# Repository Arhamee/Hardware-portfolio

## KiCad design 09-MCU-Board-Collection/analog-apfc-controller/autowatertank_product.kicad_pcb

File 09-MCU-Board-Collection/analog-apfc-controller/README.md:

# Analog Process Automation Controller

Fully analog automation system — no microcontroller, no firmware — built
entirely from discrete logic.

## Function
Automates a liquid-filling process: turns on a pump at regular intervals,
checks for flow, detects tank-full state, and safely controls AC appliances.

## How It Works
| IC | Role |
|---|---|
| NE555 #1 | 30-minute interval timer (astable) |
| NE555 #2 | Intermediate latch/controller based on flow detection |
| NE555 #3 | Final appliance state control based on sensor feedback |
| BC547 stage | Tank-full detection via probe contact sensing |
| 5× relays | Sequencing and isolation for safe AC control |

## Why This Project
A deliberate exercise in analog system design — showing what's achievable
with discrete components and timing logic alone, no code or bootloader
involved.

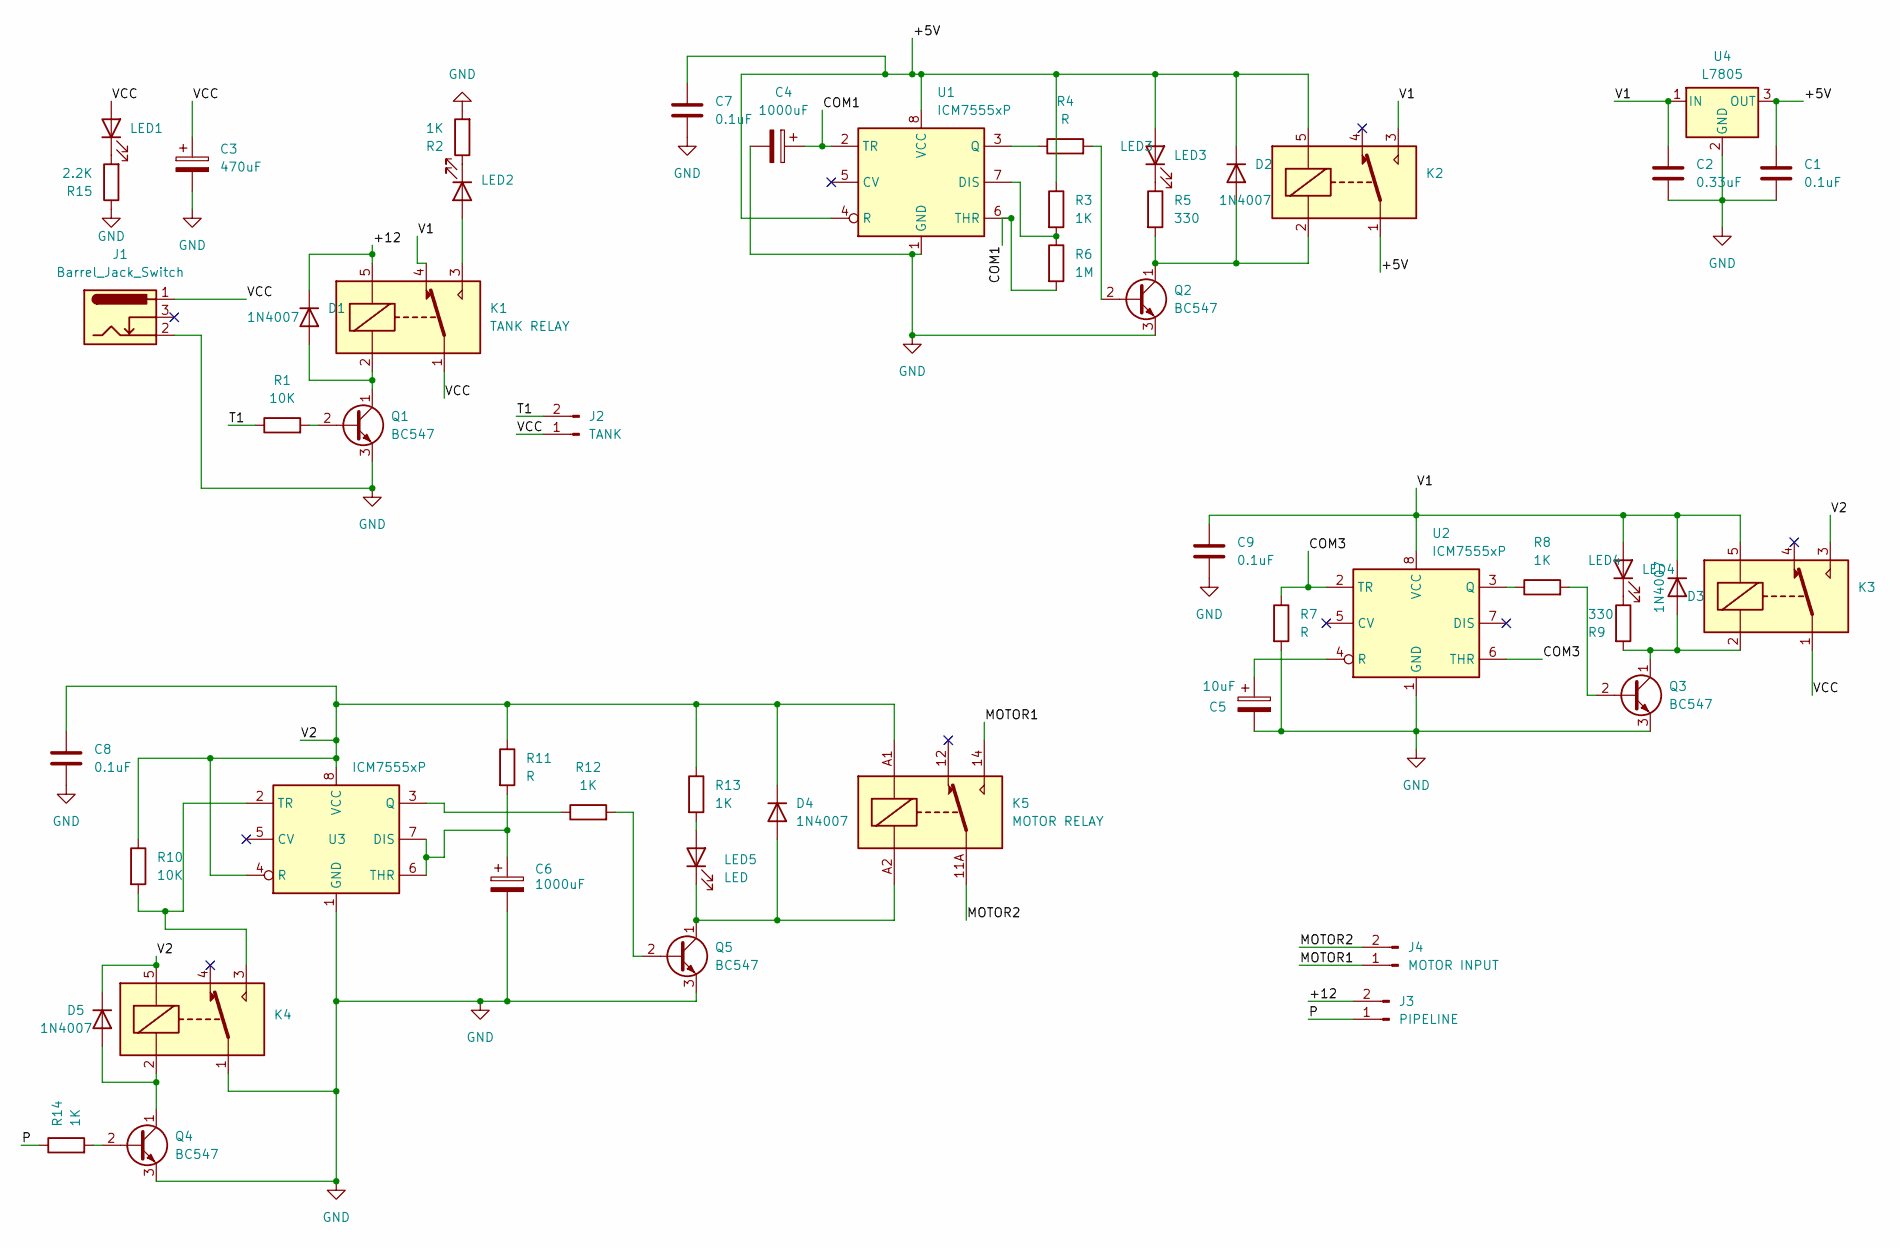
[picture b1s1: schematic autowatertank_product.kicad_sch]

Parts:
C1, C7, C8, C9: 0.1uF; C_Disc_D3.0mm_W2.0mm_P2.50mm
C2: 0.33uF; C_Disc_D3.0mm_W2.0mm_P2.50mm
C3: 470uF; CP_Radial_D8.0mm_P3.50mm
C4, C6: 1000uF; CP_Radial_D8.0mm_P5.00mm
C5: 10uF; CP_Radial_D4.0mm_P2.00mm
D1, D2, D3, D4, D5: 1N4007; D_DO-41_SOD81_P10.16mm_Horizontal
J1: Barrel_Jack_Switch; BarrelJack_GCT_DCJ200-10-A_Horizontal
J2: TANK; TerminalBlock_MaiXu_MX126-5.0-02P_1x02_P5.00mm
J3: PIPELINE; TerminalBlock_MaiXu_MX126-5.0-02P_1x02_P5.00mm
J4: MOTOR INPUT; TerminalBlock_MaiXu_MX126-5.0-02P_1x02_P5.00mm
K1: TANK RELAY; Relay_SPDT_SANYOU_SRD_Series_Form_C
K2: 555 IC RELAY 1; Relay_SPDT_SANYOU_SRD_Series_Form_C
K3, K4: Relay_SPDT_SANYOU_SRD_Series_Form_C
K5: MOTOR RELAY; Relay_SPDT_RAYEX-L90
LED1: LED_D5.0mm_Clear
LED2: FULL; LED_D5.0mm_Clear
LED3: LED3; LED_D5.0mm_Clear
LED4: LED4; LED_D5.0mm_Clear
LED5: LED; LED_D5.0mm_Clear
Q1, Q2, Q3, Q4, Q5: BC547; TO-92_Inline
R1, R10: 10K; R_Axial_DIN0207_L6.3mm_D2.5mm_P10.16mm_Horizontal
R2, R3, R8, R12, R13, R14: 1K; R_Axial_DIN0207_L6.3mm_D2.5mm_P10.16mm_Horizontal
R4, R7, R11: R; R_Axial_DIN0207_L6.3mm_D2.5mm_P10.16mm_Horizontal
R5, R9: 330; R_Axial_DIN0207_L6.3mm_D2.5mm_P10.16mm_Horizontal
R6: 1M; R_Axial_DIN0207_L6.3mm_D2.5mm_P10.16mm_Horizontal
R15: 2.2K; R_Axial_DIN0207_L6.3mm_D2.5mm_P10.16mm_Horizontal
U1, U2, U3: ICM7555xP; DIP-8_W7.62mm
U4: L7805; TO-220-3_Vertical

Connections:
/+5V: C1.1, C7.1, D2.1 (K), K2.1, K2.5, LED3.2 (A), R3.1, U1.4 (R), U1.8 (VCC), U4.3 (OUT)
/+12: D1.1 (K), J3.2, K1.5
/COM1: C4.1, R6.2, U1.2 (TR), U1.6 (THR)
/COM3: R7.1, U2.2 (TR), U2.6 (THR)
/MOTOR1: J4.1, K5.14
/MOTOR2: J4.2, K5.11A, K5.11B
/P: J3.1, R14.1
/T1: J2.2, R1.1
/V1: C2.1, C9.1, D3.1 (K), K1.4, K2.3, K3.5, LED4.2 (A), U2.8 (VCC), U4.1 (IN)
/V2: C8.1, D4.1 (K), D5.1 (K), K3.3, K4.5, K5.A1, R10.1, R11.1, R13.1, U3.4 (R), U3.8 (VCC)
/VCC: C3.1, J1.1, J2.1, K1.1, K3.1, LED1.2 (A)
GND: C1.2, C2.2, C3.2, C4.2, C5.2, C6.2, C7.2, C8.2, C9.2, J1.2, K4.1, Q1.3 (E), Q2.3 (E), Q3.3 (E), Q4.3 (E), Q5.3 (E), R2.2, R7.2, R15.1, U1.1 (GND), U2.1 (GND), U3.1 (GND), U4.2 (GND)
unnamed: D1.2 (A), K1.2, Q1.1 (C)
unnamed: D2.2 (A), K2.2, Q2.1 (C), R5.2
unnamed: D3.2 (A), K3.2, Q3.1 (C), R9.2
unnamed: D4.2 (A), K5.A2, LED5.1 (K), Q5.1 (C)
unnamed: D5.2 (A), K4.2, Q4.1 (C)
unnamed: LED1.1 (K), R15.2
unnamed: K1.3, LED2.2 (A)
unnamed: LED2.1 (K), R2.1
unnamed: LED3.1 (K), R5.1
unnamed: LED4.1 (K), R9.1
unnamed: LED5.2 (A), R13.2
unnamed: Q1.2 (B), R1.2
unnamed: Q2.2 (B), R4.2
unnamed: Q3.2 (B), R8.2
unnamed: Q4.2 (B), R14.2
unnamed: Q5.2 (B), R12.2
unnamed: R3.2, R6.1, U1.7 (DIS)
unnamed: R4.1, U1.3 (Q)
unnamed: R8.1, U2.3 (Q)
unnamed: C5.1, U2.4 (R)
unnamed: C6.1, R11.2, U3.6 (THR), U3.7 (DIS)
unnamed: R12.1, U3.3 (Q)
unnamed: K4.3, R10.2, U3.2 (TR)

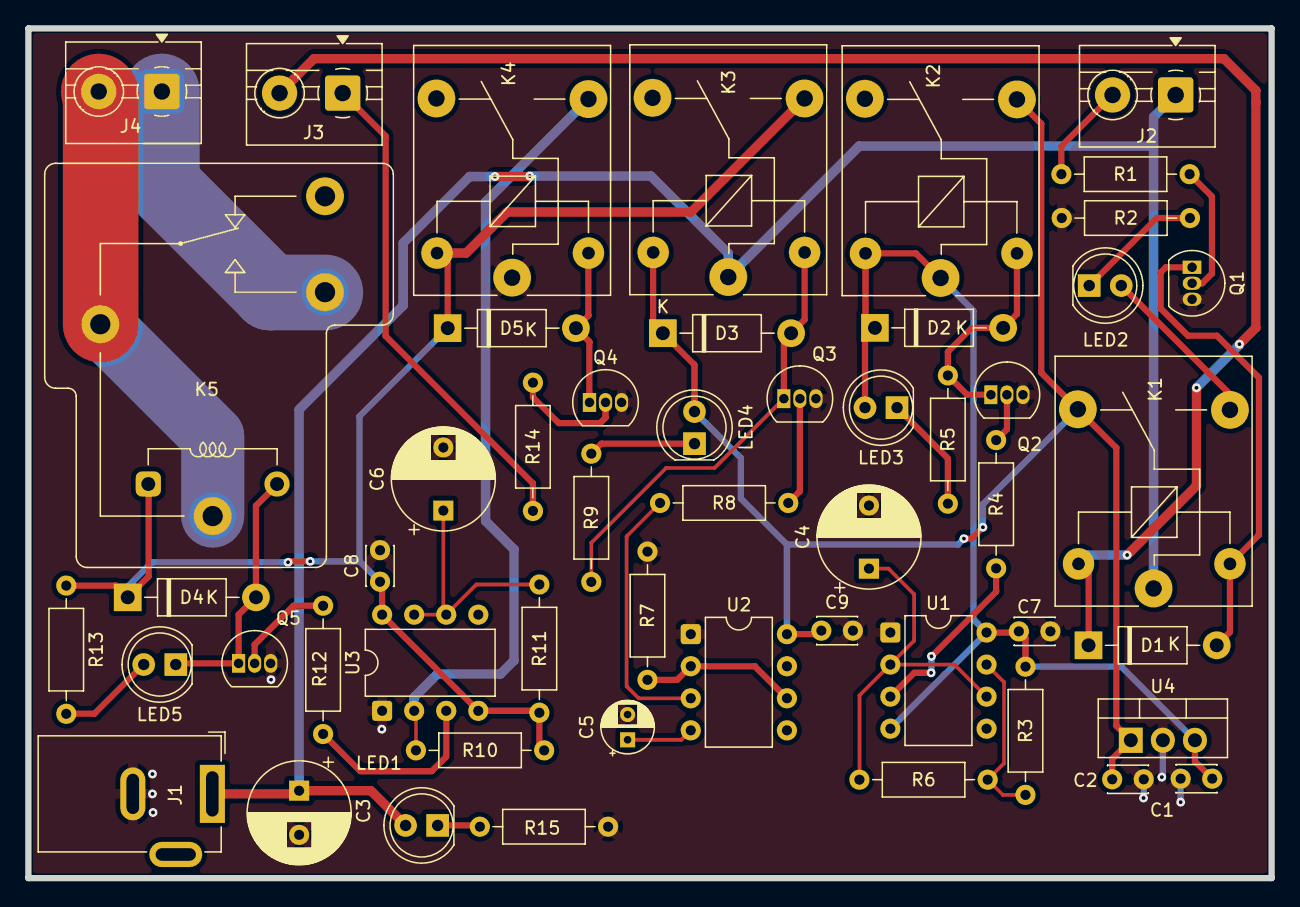
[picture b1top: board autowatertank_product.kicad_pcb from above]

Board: 2 copper layers, 98.5 x 67.3 mm, 52 parts (0 on the bottom side), 35 nets.

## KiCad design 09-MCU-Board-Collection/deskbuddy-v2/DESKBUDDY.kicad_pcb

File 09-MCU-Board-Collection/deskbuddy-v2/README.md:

# DeskBuddy v2

Custom PCB replacing a breadboard prototype's separate modules with a
single integrated board.

## What Got Replaced
- Separate charging module → **IP5306** (charges, protects, and boosts to 5V — one chip)
- Standalone touch sensor breakout → **TTP223** etched directly onto the board
- Breakout boards and jumper wires → clean, compact PCB

## Features
- ESP32-C3 + OLED display
- Live battery indicator on-screen
- Animated eyes with expressions
- Real-time weather with custom icons
- Auto-syncing clock (timezone-aware)
- Birthday celebration mode

## Note
Started as "let me make my desk less boring" — turned into a full PCB
design exercise in component integration and board miniaturization.

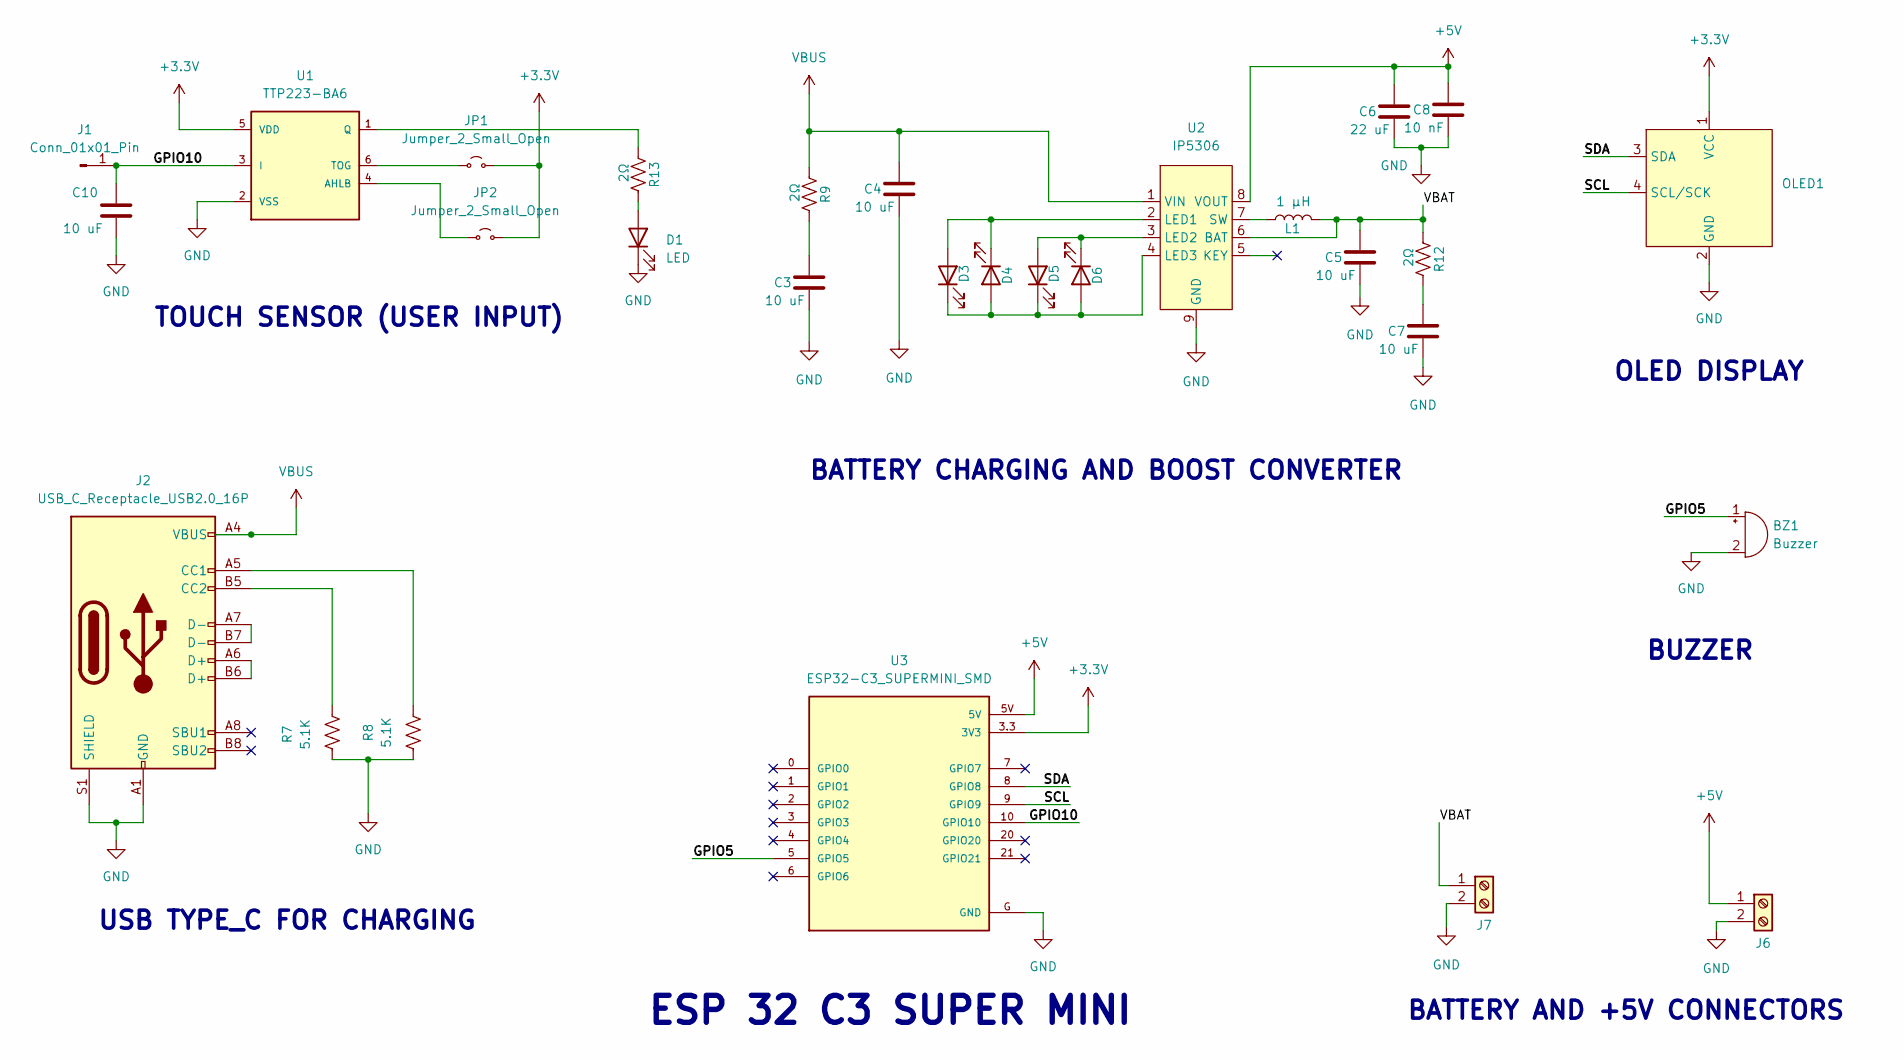
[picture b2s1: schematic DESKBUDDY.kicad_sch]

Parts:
BZ1: Buzzer; Buzzer_12x9.5RM7.6
C3, C4, C5, C7: 10 uF; C_1206_3216Metric_Pad1.33x1.80mm_HandSolder
C6: 22 uF; C_1206_3216Metric_Pad1.33x1.80mm_HandSolder
C8: 10 nF; C_1206_3216Metric_Pad1.33x1.80mm_HandSolder
C10: 10 uF; C_0805_2012Metric_Pad1.18x1.45mm_HandSolder
D1: LED; D_0805_2012Metric_Pad1.15x1.40mm_HandSolder
D3, D4, D5, D6: Blue LED; LED_1206_3216Metric
J1: Conn_01x01_Pin; TestPoint_Pad_D4.0mm
J2: USB_C_Receptacle_USB2.0_16P; USB_C_Receptacle_GCT_USB4105-xx-A_16P_TopMnt_Horizontal
J6, J7: Terminal_01x02; PinHeader_1x02_P2.00mm_Vertical
JP1, JP2: Jumper_2_Small_Open; SolderJumper-2_P1.3mm_Open_Pad1.0x1.5mm
L1: 1 µH; L_Sunlord_SWPA6028S
OLED1: PinSocket_1x04_P2.00mm_Vertical
R7, R8: 5.1K; R_1206_3216Metric
R9, R12: 2Ω; R_1206_3216Metric
R13: 2Ω; R_0805_2012Metric_Pad1.20x1.40mm_HandSolder
U1: TTP223-BA6; SOT23-6
U2: IP5306; SOP-8-1EP_4.57x4.57mm_P1.27mm_EP4.57x4.45mm_ThermalVias
U3: ESP32-C3_SUPERMINI_SMD; MODULE_ESP32-C3_SUPERMINI

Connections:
+3.3V: JP1.2 (B), JP2.2 (B), OLED1.1 (VCC), U1.5 (VDD), U3.3.3 (3V3)
+5V: C6.1, C8.1, J6.1, U2.8 (VOUT), U3.5V
/GPIO5: BZ1.1 (+), U3.5 (GPIO5)
/GPIO10: C10.1, J1.1, U1.3 (I), U3.10 (GPIO10)
/SCL: OLED1.4 (SCL/SCK), U3.9 (GPIO9)
/SDA: OLED1.3 (SDA), U3.8 (GPIO8)
/VBAT: C5.1, J7.1, L1.2, R12.1, U2.6 (BAT)
GND: BZ1.2 (-), C3.2, C4.2, C5.2, C6.2, C7.2, C8.2, C10.2, D1.1 (K), J2.A1 (GND), J2.A12 (GND), J2.B1 (GND), J2.B12 (GND), J2.S1 (SHIELD), J6.2, J7.2, OLED1.2 (GND), R7.1, R8.1, U1.2 (VSS), U2.9 (GND), U3.G (GND)
unnamed: C3.1, R9.2
unnamed: C7.1, R12.2
unnamed: D1.2 (A), R13.2
unnamed: D3.2 (A), D4.1 (K), U2.2 (LED1)
unnamed: D3.1 (K), D4.2 (A), D5.1 (K), D6.2 (A), U2.4 (LED3)
unnamed: D5.2 (A), D6.1 (K), U2.3 (LED2)
unnamed: J2.A5 (CC1), R8.2
unnamed: J2.B5 (CC2), R7.2
unnamed: J2.A6 (D+), J2.B6 (D+)
unnamed: J2.A7 (D-), J2.B7 (D-)
unnamed: JP1.1 (A), U1.6 (TOG)
unnamed: JP2.1 (A), U1.4 (AHLB)
unnamed: R13.1, U1.1 (Q)
unnamed: L1.1, U2.7 (SW)
VBUS: C4.1, J2.A4 (VBUS), J2.A9 (VBUS), J2.B4 (VBUS), J2.B9 (VBUS), R9.1, U2.1 (VIN)

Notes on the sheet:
TOUCH SENSOR (USER INPUT)
BATTERY CHARGING AND BOOST CONVERTER
OLED DISPLAY
BATTERY AND +5V CONNECTORS
USB TYPE_C FOR CHARGING
ESP 32 C3 SUPER MINI
BUZZER

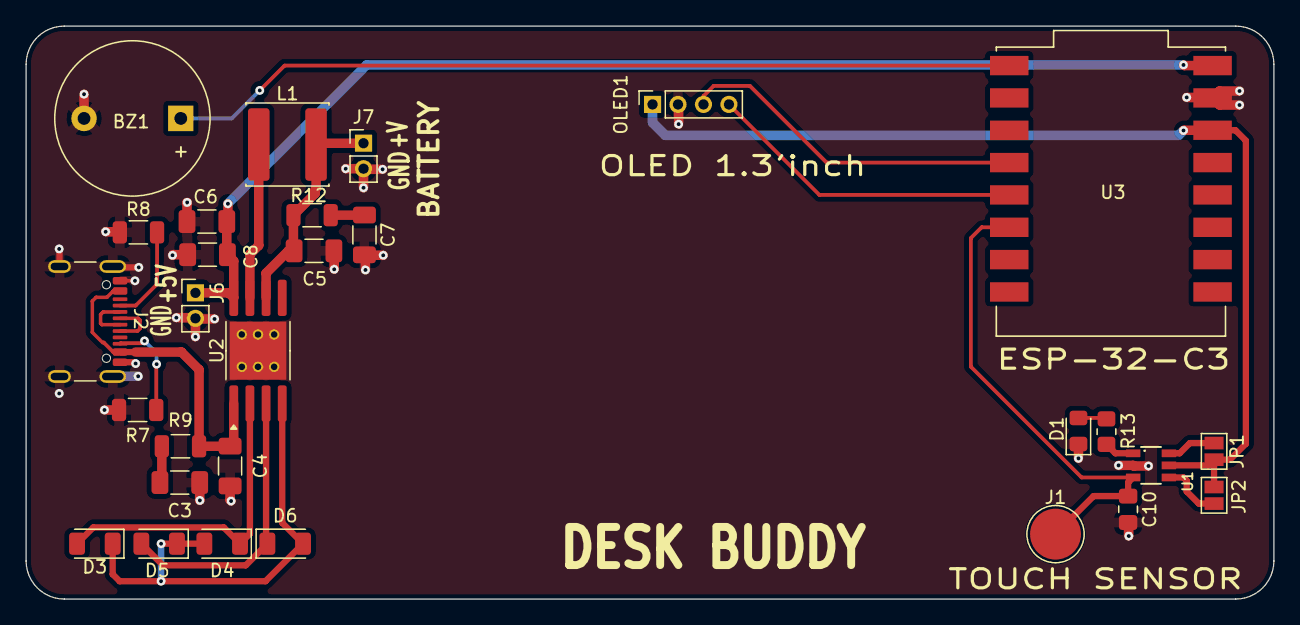
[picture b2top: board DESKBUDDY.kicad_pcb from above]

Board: 2 copper layers, 98.0 x 45.0 mm, 29 parts (0 on the bottom side), 23 nets.

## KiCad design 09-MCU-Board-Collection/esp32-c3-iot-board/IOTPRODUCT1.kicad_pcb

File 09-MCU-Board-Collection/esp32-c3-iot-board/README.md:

# IoT Control Board — ESP32-C3

Custom board combining power electronics and embedded IoT into one design,
plus a companion programming board.

## Power Path
12V input → boost converter → 5V → 3.3V regulation for the ESP32-C3

## Features
- Handles up to 5A load
- Onboard fuse protection
- Integrated T90 relay for high-power switching
- Dashboard integration (QWIN AI) for real-time monitoring and control

## Bonus
A separate USB-to-UART programming board, built alongside this one, for
seamless firmware uploading and debugging.

## What This Covered
End-to-end IoT product design — power management, protection, communication,
and control — not just the MCU layout.

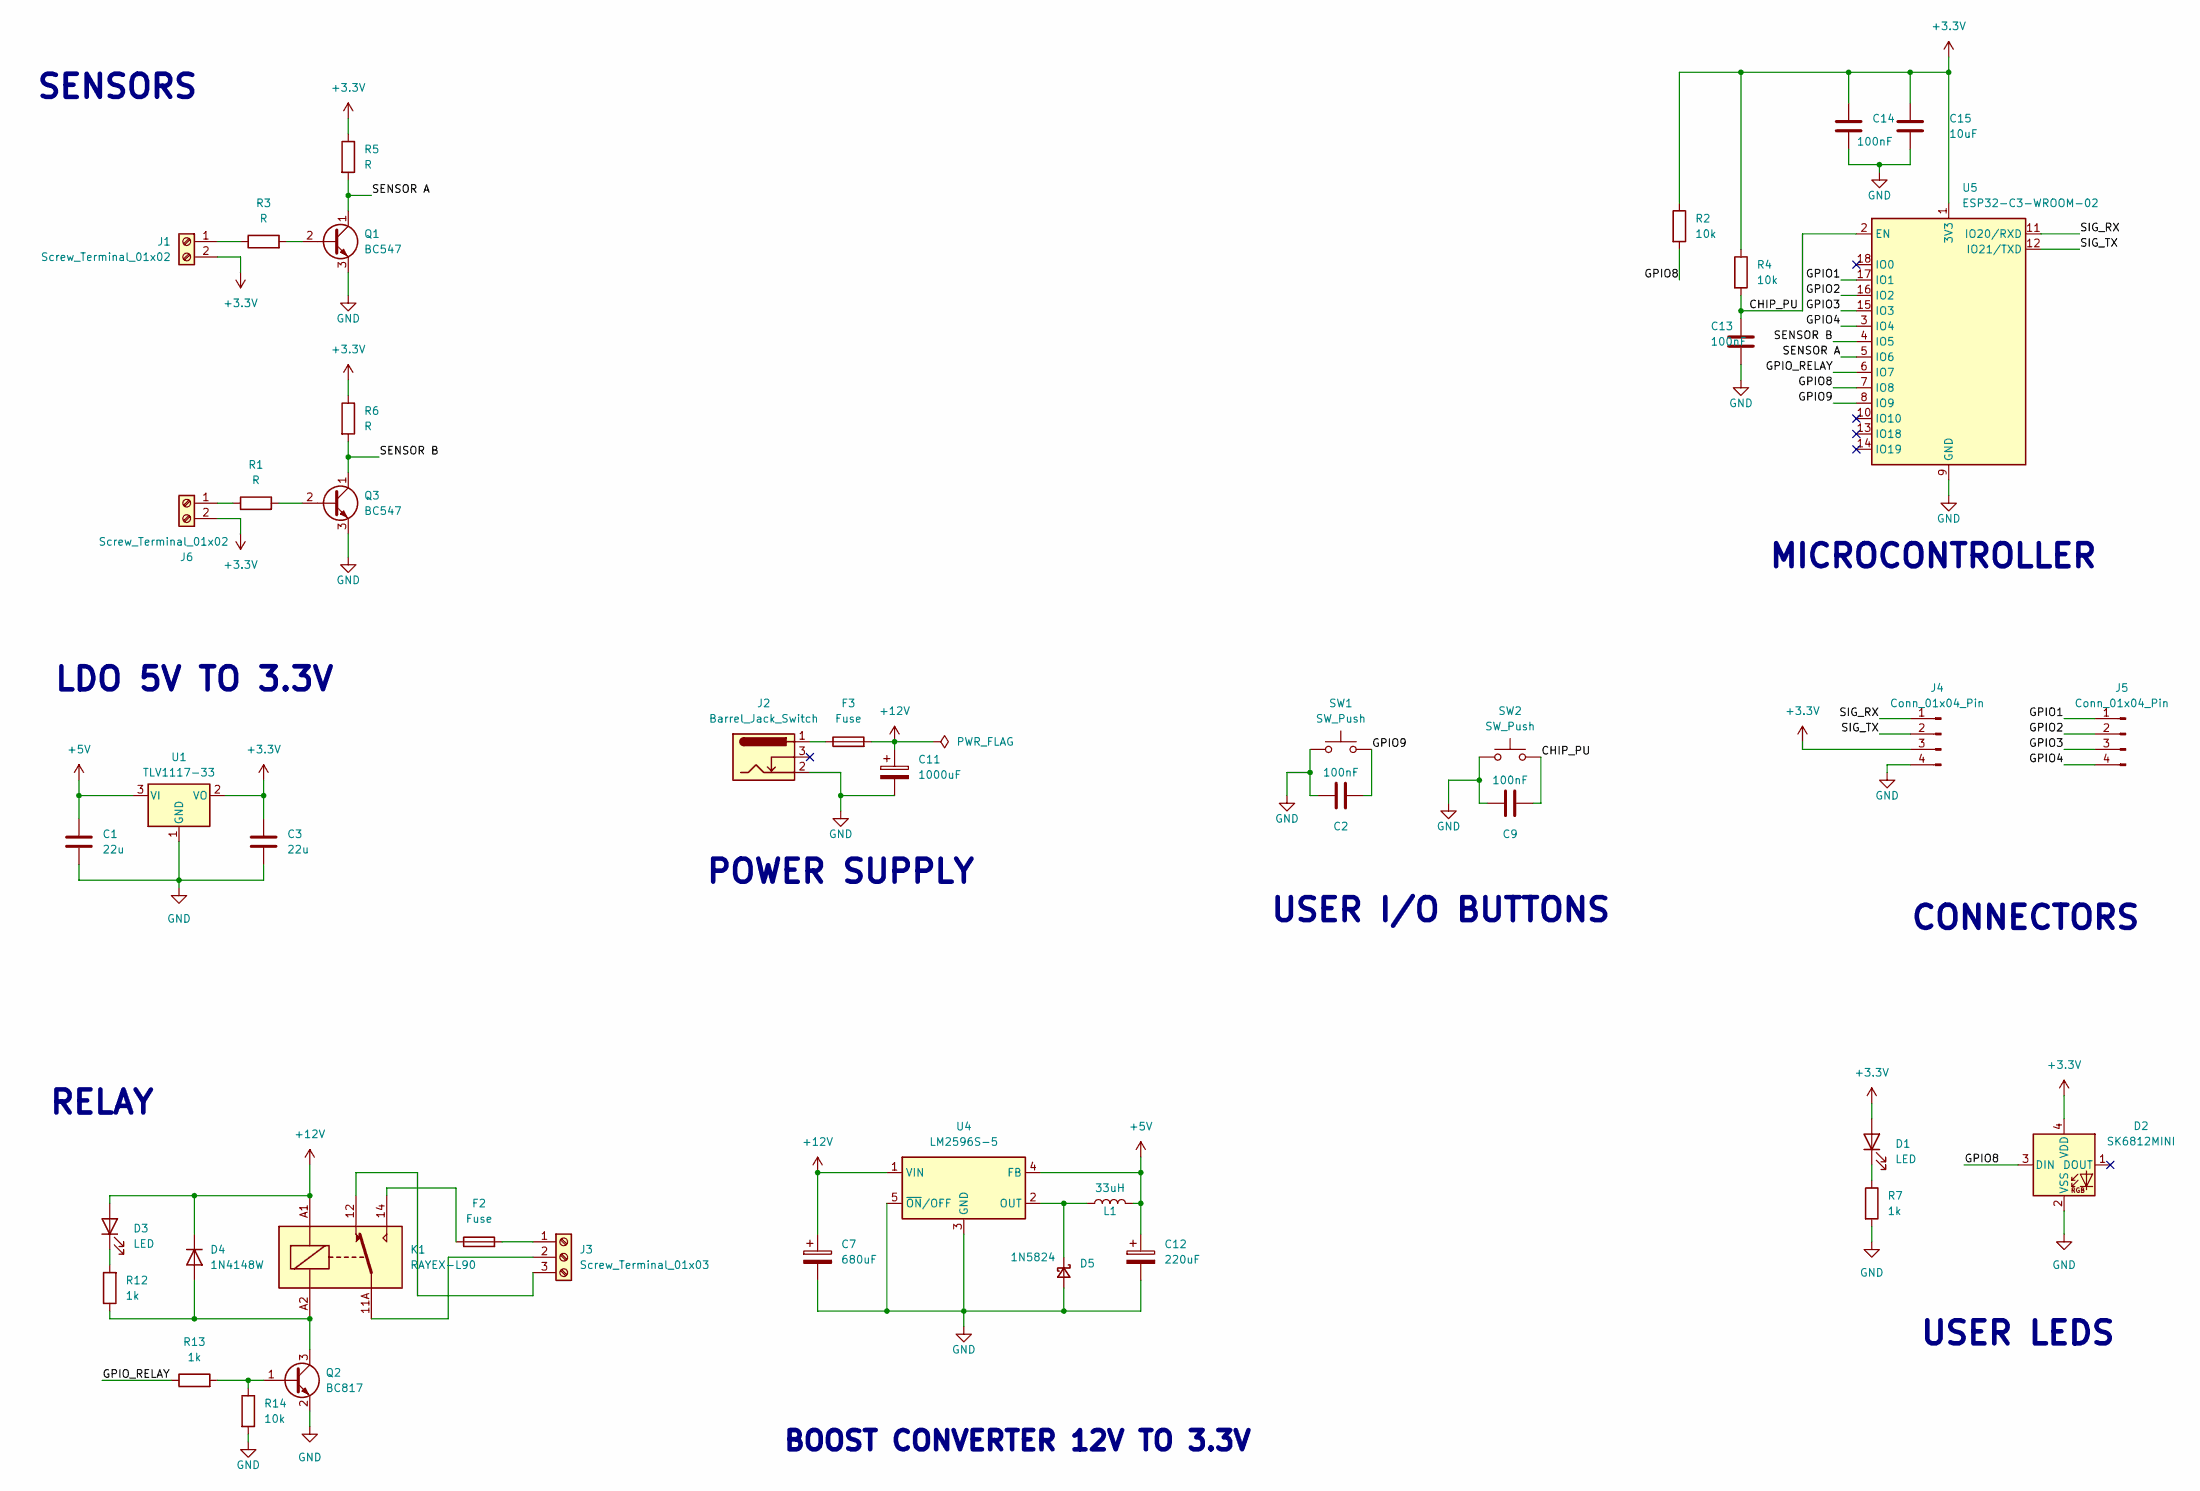
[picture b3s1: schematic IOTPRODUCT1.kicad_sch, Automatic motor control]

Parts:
C1, C3: 22u; C_0805_2012Metric_Pad1.18x1.45mm_HandSolder
C2, C9, C13, C14: 100nF; C_0402_1005Metric_Pad0.74x0.62mm_HandSolder
C7: 680uF; CP_Radial_D7.5mm_P2.50mm
C11: 1000uF; CP_Radial_D8.0mm_P3.50mm
C12: 220uF; CP_Radial_D6.3mm_P2.50mm
C15: 10uF; C_0603_1608Metric_Pad1.08x0.95mm_HandSolder
D1, D3: LED; LED_0402_1005Metric_Pad0.77x0.64mm_HandSolder
D2: SK6812MINI; LED_SK6812MINI_PLCC4_3.5x3.5mm_P1.75mm
D4: 1N4148W; D_SOD-123
D5: 1N5824; D_0603_1608Metric_Pad1.05x0.95mm_HandSolder
F2: Fuse; FUSE_696105003002
F3: Fuse; Fuse_1210_3225Metric_Pad1.42x2.65mm_HandSolder
J1, J6: Screw_Terminal_01x02; TerminalBlock_Phoenix_MKDS-1,5-2-5.08_1x02_P5.08mm_Horizont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
J2: Barrel_Jack_Switch; BarrelJack_Horizontal
J3: Screw_Terminal_01x03; TerminalBlock_Phoenix_MKDS-1,5-3_1x03_P5.00mm_Horizontal
J4, J5: Conn_01x04_Pin; PinHeader_1x04_P2.54mm_Vertical
K1: RAYEX-L90; Relay_SPDT_RAYEX-L90
L1: 33uH; L_Changjiang_FNR4015S
Q1, Q3: BC547; TO-92_Inline
Q2: BC817; SOT-23
R1, R3, R5, R6: R; R_0402_1005Metric_Pad0.72x0.64mm_HandSolder
R2, R4, R14: 10k; R_0402_1005Metric_Pad0.72x0.64mm_HandSolder
R7, R12, R13: 1k; R_0402_1005Metric_Pad0.72x0.64mm_HandSolder
SW1, SW2: SW_Push; SW_Tactile_SPST_NO_Straight_CK_PTS636Sx25SMTRLFS
U1: TLV1117-33; SOT-223-3_TabPin2
U4: LM2596S-5; TO-263-5_TabPin3
U5: ESP32-C3-WROOM-02

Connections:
+3.3V: C3.1, C14.1, C15.1, D1.2 (A), D2.4 (VDD), J1.2, J4.3, J6.2, R2.1, R4.1, R5.1, R6.1, U1.2 (VO), U5.1 (3V3)
+5V: C1.1, C12.1, L1.2, U1.3 (VI), U4.4 (FB)
+12V: C7.1, C11.1, D3.2 (A), D4.1 (K), F3.2, K1.A1, U4.1 (VIN)
/CHIP_PU: C9.2, C13.1, R4.2, SW2.2, U5.2 (EN)
/GPIO1: J5.1, U5.17 (IO1)
/GPIO2: J5.2, U5.16 (IO2)
/GPIO3: J5.3, U5.15 (IO3)
/GPIO4: J5.4, U5.3 (IO4)
/GPIO8: D2.3 (DIN), R2.2, U5.7 (IO8)
/GPIO9: C2.2, SW1.2, U5.8 (IO9)
/GPIO_RELAY: R13.1, U5.6 (IO7)
/SENSOR A: Q1.1 (C), R5.2, U5.5 (IO6)
/SENSOR B: Q3.1 (C), R6.2, U5.4 (IO5)
/SIG_RX: J4.1, U5.11 (IO20/RXD)
/SIG_TX: J4.2, U5.12 (IO21/TXD)
GND: C1.2, C2.1, C3.2, C7.2, C9.1, C11.2, C12.2, C13.2, C14.2, C15.2, D2.2 (VSS), D5.2 (A), J2.2, J4.4, Q1.3 (E), Q2.2 (E), Q3.3 (E), R7.2, R14.2, SW1.1, SW2.1, U1.1 (GND), U4.3 (GND), U4.5 (~ON/OFF), U5.9 (GND), U5.19 (GND)
unnamed: D1.1 (K), R7.1
unnamed: D3.1 (K), R12.2
unnamed: D4.2 (A), K1.A2, Q2.3 (C), R12.1
unnamed: D5.1 (K), L1.1, U4.2 (OUT)
unnamed: F2.1, K1.14
unnamed: F3.1, J2.1
unnamed: J1.1, R3.1
unnamed: F2.2, J3.1
unnamed: J3.2, K1.11A, K1.11B
unnamed: J3.3, K1.12
unnamed: J6.1, R1.1
unnamed: Q1.2 (B), R3.2
unnamed: Q2.1 (B), R13.2, R14.1
unnamed: Q3.2 (B), R1.2

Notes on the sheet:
SENSORS
MICROCONTROLLER
CONNECTORS
RELAY
LDO 5V TO 3.3V
BOOST CONVERTER 12V TO 3.3V
USER LEDS
POWER SUPPLY
USER I/O BUTTONS

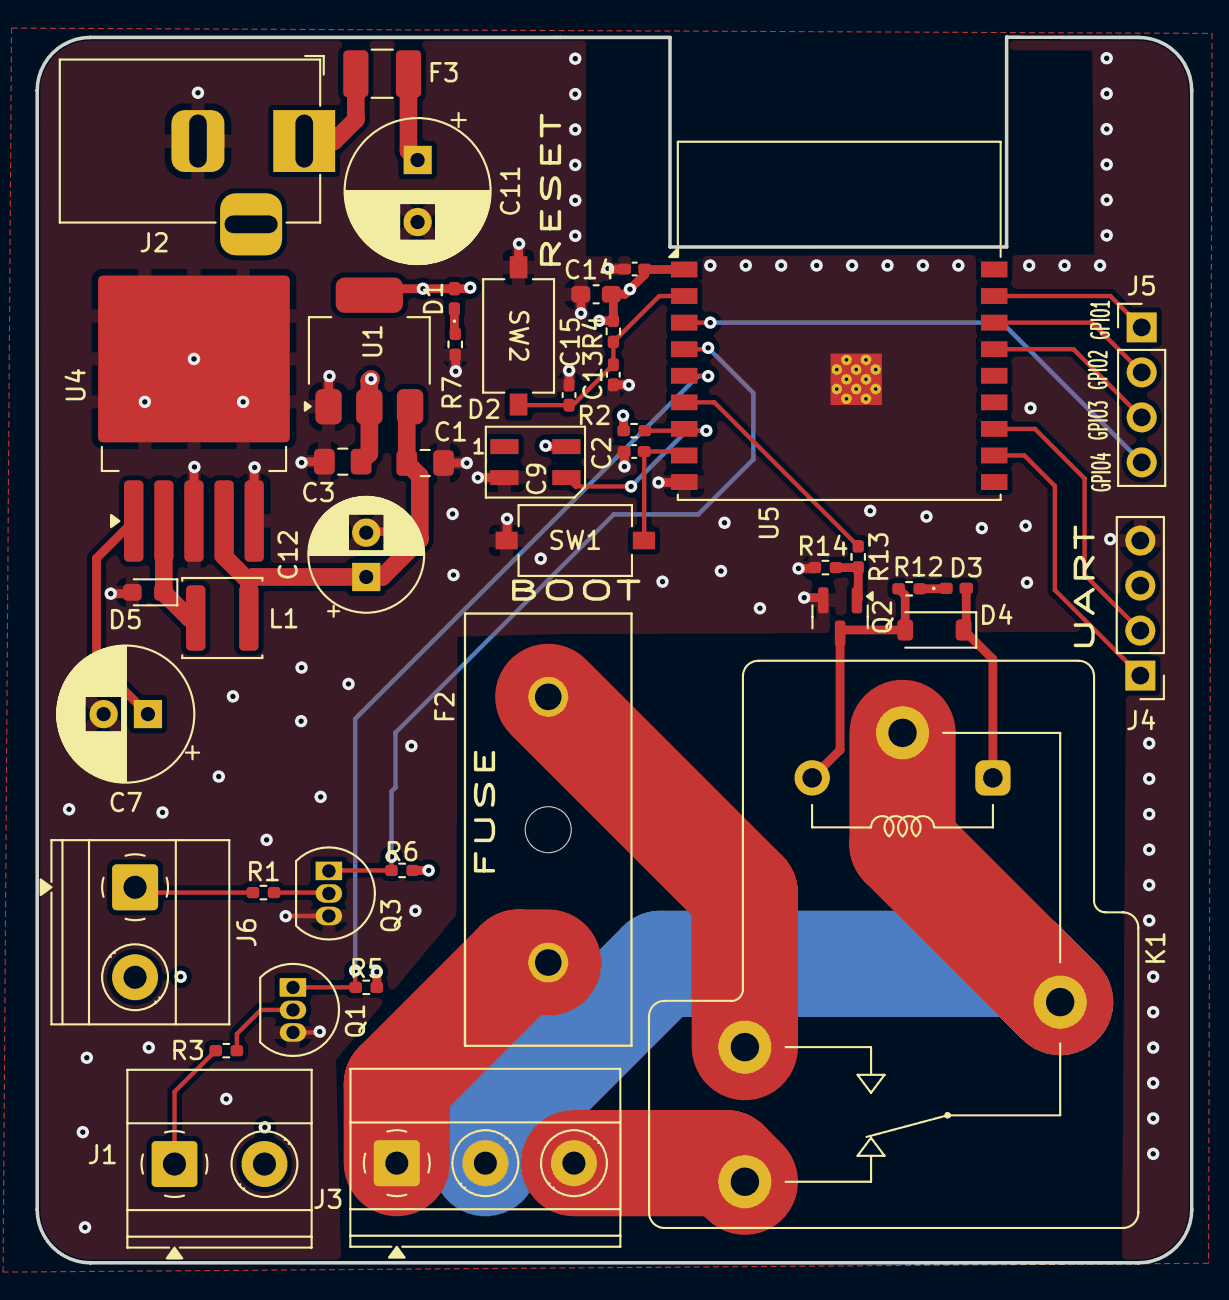
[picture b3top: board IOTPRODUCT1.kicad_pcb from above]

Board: 4 copper layers, 65.2 x 69.2 mm, 43 parts (0 on the bottom side), 30 nets.

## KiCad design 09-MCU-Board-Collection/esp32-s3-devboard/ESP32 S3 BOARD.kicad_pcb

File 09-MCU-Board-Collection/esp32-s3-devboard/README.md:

# IoT Dev Board — ESP32-S3 (8MB Flash)

4-layer board built for speed and scalability in IoT/edge projects.

## Features
- ESP32-S3, 8MB flash
- Si7021 temperature/humidity sensor
- USB-C for power and programming
- QWIIC and SPI expansion headers
- BOOT/RESET buttons, RGB LED status

## Stackup
Clean 4-layer design balancing signal integrity and thermal efficiency —
intended as a reusable base for future sensor/edge-device projects.

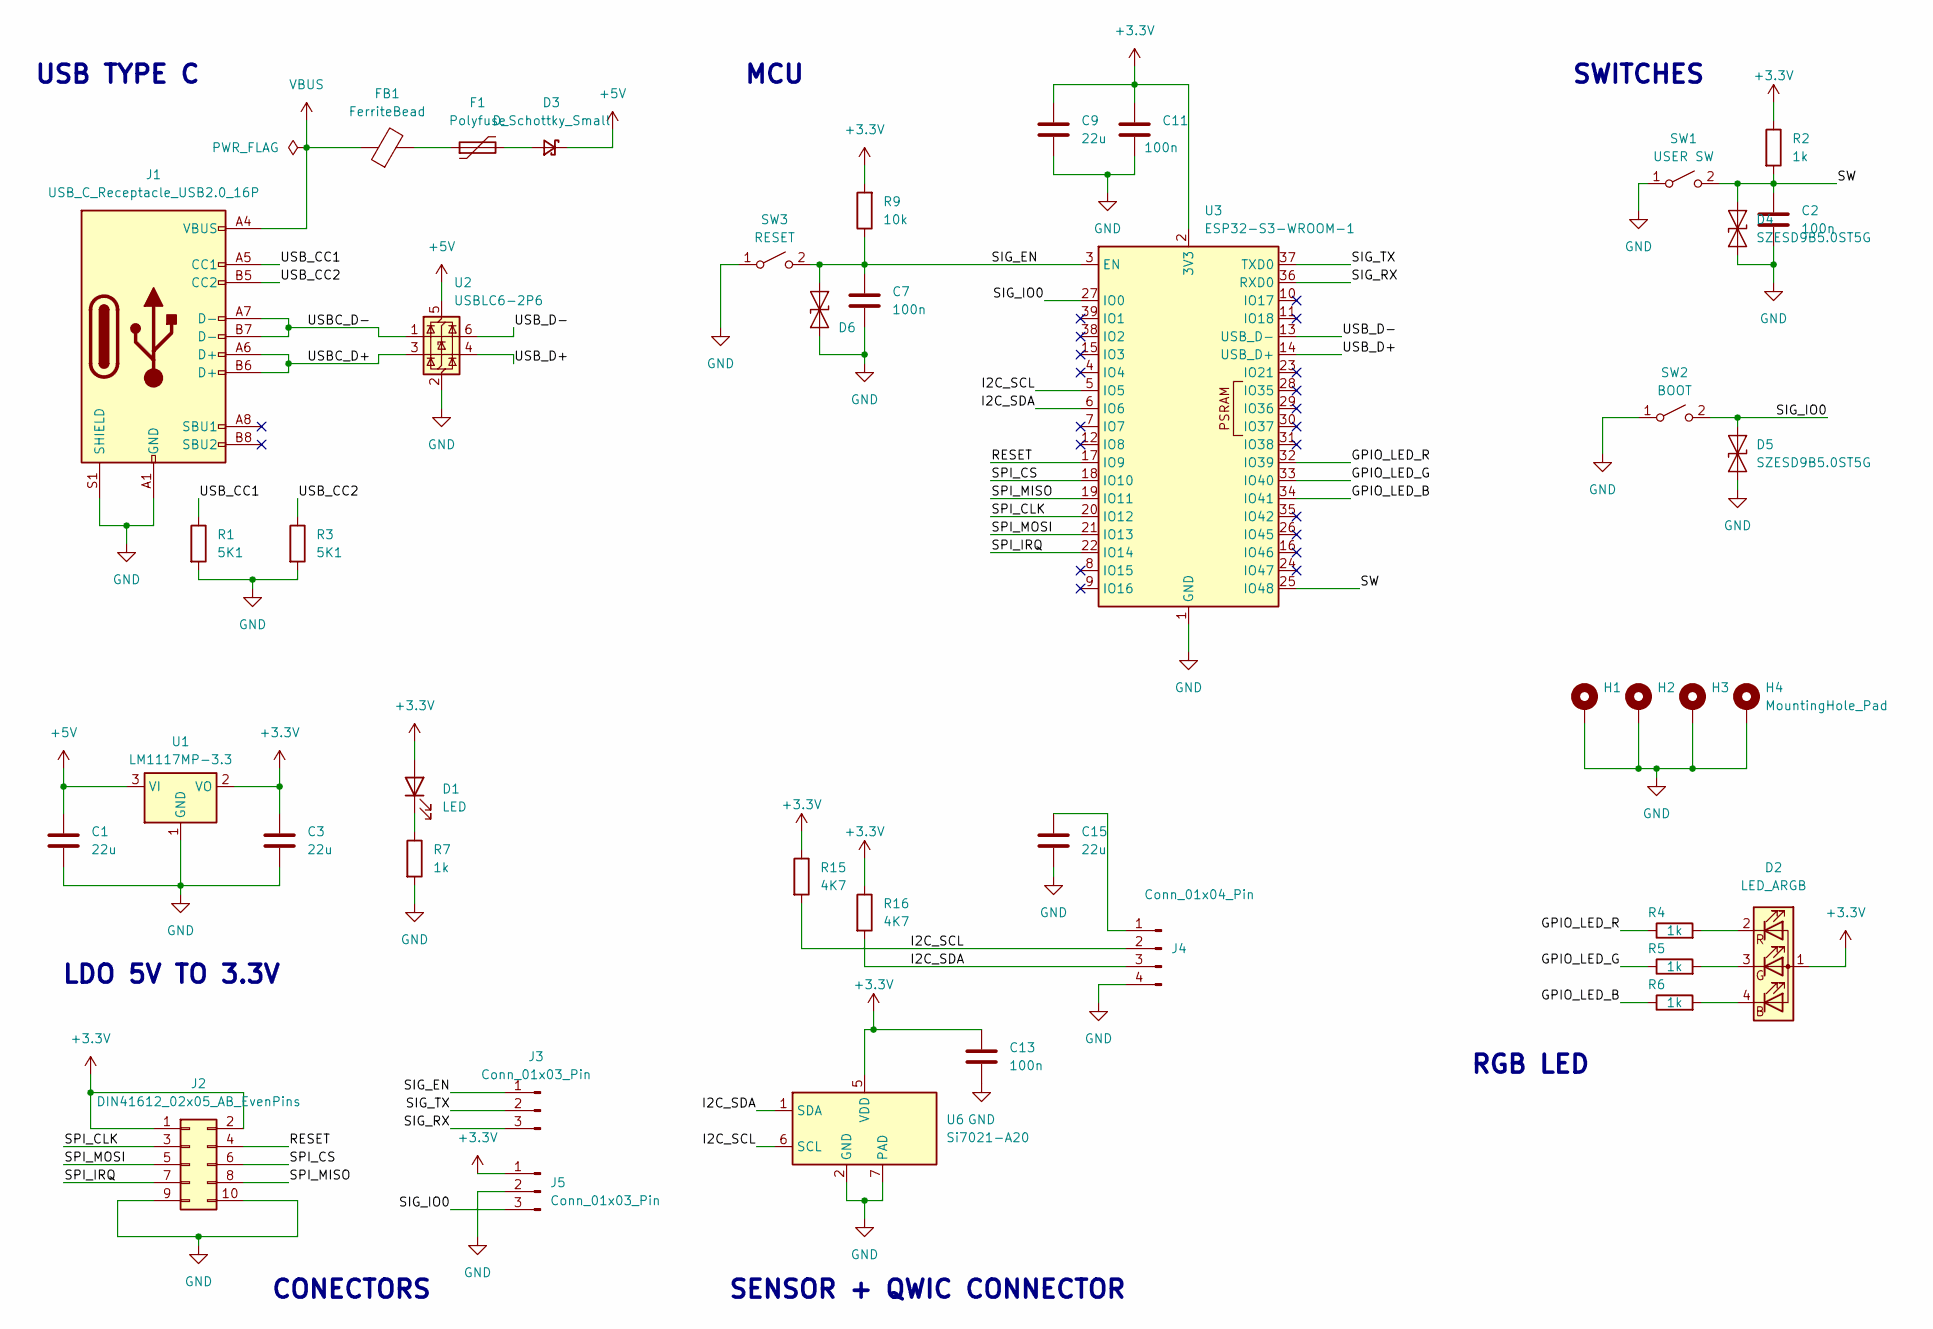
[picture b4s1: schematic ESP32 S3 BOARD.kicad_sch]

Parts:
C1, C3, C9, C15: 22u; C_0805_2012Metric_Pad1.18x1.45mm_HandSolder
C2, C7, C11, C13: 100n; C_0402_1005Metric_Pad0.74x0.62mm_HandSolder
D1: LED; LED_0402_1005Metric_Pad0.77x0.64mm_HandSolder
D2: LED_ARGB; LED_Cree-PLCC4_3.2x2.8mm_CCW
D3: D_Schottky_Small; D_0603_1608Metric_Pad1.05x0.95mm_HandSolder
D4, D5, D6: SZESD9B5.0ST5G; D_SOD-923
F1: Polyfuse; Fuse_1206_3216Metric_Pad1.42x1.75mm_HandSolder
FB1: FerriteBead; L_0603_1608Metric_Pad1.05x0.95mm_HandSolder
H1, H2, H3, H4: MountingHole_Pad; MountingHole_2.2mm_M2_DIN965_Pad
J1: USB_C_Receptacle_USB2.0_16P; USB_C_Receptacle_GCT_USB4105-xx-A_16P_TopMnt_Horizontal
J2: DIN41612_02x05_AB_EvenPins; PinHeader_2x05_P2.54mm_Vertical
J3, J5: Conn_01x03_Pin; PinHeader_1x03_P2.54mm_Vertical
J4: Conn_01x04_Pin; Molex_PicoBlade_53048-0410_1x04_P1.25mm_Horizontal
R1, R3: 5K1; R_0402_1005Metric_Pad0.72x0.64mm_HandSolder
R2, R4, R5, R6, R7: 1k; R_0402_1005Metric_Pad0.72x0.64mm_HandSolder
R9: 10k; R_0402_1005Metric_Pad0.72x0.64mm_HandSolder
R15, R16: 4K7; R_0402_1005Metric_Pad0.72x0.64mm_HandSolder
SW1: USER SW; SW_SPST_CK_RS282G05A3
SW2: BOOT; SW_SPST_CK_RS282G05A3
SW3: RESET; SW_SPST_CK_RS282G05A3
U1: LM1117MP-3.3; SOT-223-3_TabPin2
U2: USBLC6-2P6; SOT-666
U3: ESP32-S3-WROOM-1
U6: Si7021-A20; DFN-6-1EP_3x3mm_P1mm_EP1.5x2.4mm

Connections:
+3.3V: C3.1, C9.1, C11.1, C13.1, D1.2 (A), D2.1 (A), J2.1 (Pin_a2), J2.2 (Pin_b2), J5.1, R2.1, R9.2, R15.1, R16.1, U1.2 (VO), U3.2 (3V3), U6.5 (VDD)
+5V: C1.1, D3.1 (K), U1.3 (VI), U2.5 (VBUS)
/GPIO_LED_B: R6.1, U3.34 (IO41)
/GPIO_LED_G: R5.1, U3.33 (IO40)
/GPIO_LED_R: R4.1, U3.32 (IO39)
/I2C_SCL: J4.2, R15.2, U3.5 (IO5), U6.6 (SCL)
/I2C_SDA: J4.3, R16.2, U3.6 (IO6), U6.1 (SDA)
/RESET: J2.4 (Pin_b4), U3.17 (IO9)
/SIG_EN: C7.2, D6.2 (A2), J3.1, R9.1, SW3.2 (B), U3.3 (EN)
/SIG_IO0: D5.2 (A2), J5.3, SW2.2 (B), U3.27 (IO0)
/SIG_RX: J3.3, U3.36 (RXD0)
/SIG_TX: J3.2, U3.37 (TXD0)
/SPI_CLK: J2.3 (Pin_a4), U3.20 (IO12)
/SPI_CS: J2.6 (Pin_b6), U3.18 (IO10)
/SPI_IRQ: J2.7 (Pin_a8), U3.22 (IO14)
/SPI_MISO: J2.8 (Pin_b8), U3.19 (IO11)
/SPI_MOSI: J2.5 (Pin_a6), U3.21 (IO13)
/SW: C2.1, D4.2 (A2), R2.2, SW1.2 (B), U3.25 (IO48)
/USBC_D+: J1.A6 (D+), J1.B6 (D+), U2.3 (I/O2)
/USBC_D-: J1.A7 (D-), J1.B7 (D-), U2.1 (I/O1)
/USB_CC1: J1.A5 (CC1), R1.1
/USB_CC2: J1.B5 (CC2), R3.1
/USB_D+: U2.4 (I/O2), U3.14 (USB_D+)
/USB_D-: U2.6 (I/O1), U3.13 (USB_D-)
GND: C1.2, C2.2, C3.2, C7.1, C9.2, C11.2, C13.2, C15.2, D4.1 (A1), D5.1 (A1), D6.1 (A1), H1.1, H2.1, H3.1, H4.1, J1.A1 (GND), J1.A12 (GND), J1.B1 (GND), J1.B12 (GND), J1.S1 (SHIELD), J2.9 (Pin_a10), J2.10 (Pin_b10), J4.4, J5.2, R1.2, R3.2, R7.2, SW1.1 (A), SW2.1 (A), SW3.1 (A), U1.1 (GND), U2.2 (GND), U3.1 (GND), U3.40 (GND), U3.41 (GND), U6.2 (GND), U6.7 (PAD)
unnamed: D1.1 (K), R7.1
unnamed: D2.4 (BK), R6.2
unnamed: D2.3 (GK), R5.2
unnamed: D2.2 (RK), R4.2
unnamed: D3.2 (A), F1.2
unnamed: F1.1, FB1.2
unnamed: C15.1, J4.1
VBUS: FB1.1, J1.A4 (VBUS), J1.A9 (VBUS), J1.B4 (VBUS), J1.B9 (VBUS)

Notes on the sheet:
LDO 5V TO 3.3V
USB TYPE C
CONECTORS
SWITCHES
MCU
SENSOR + QWIC CONNECTOR
RGB LED

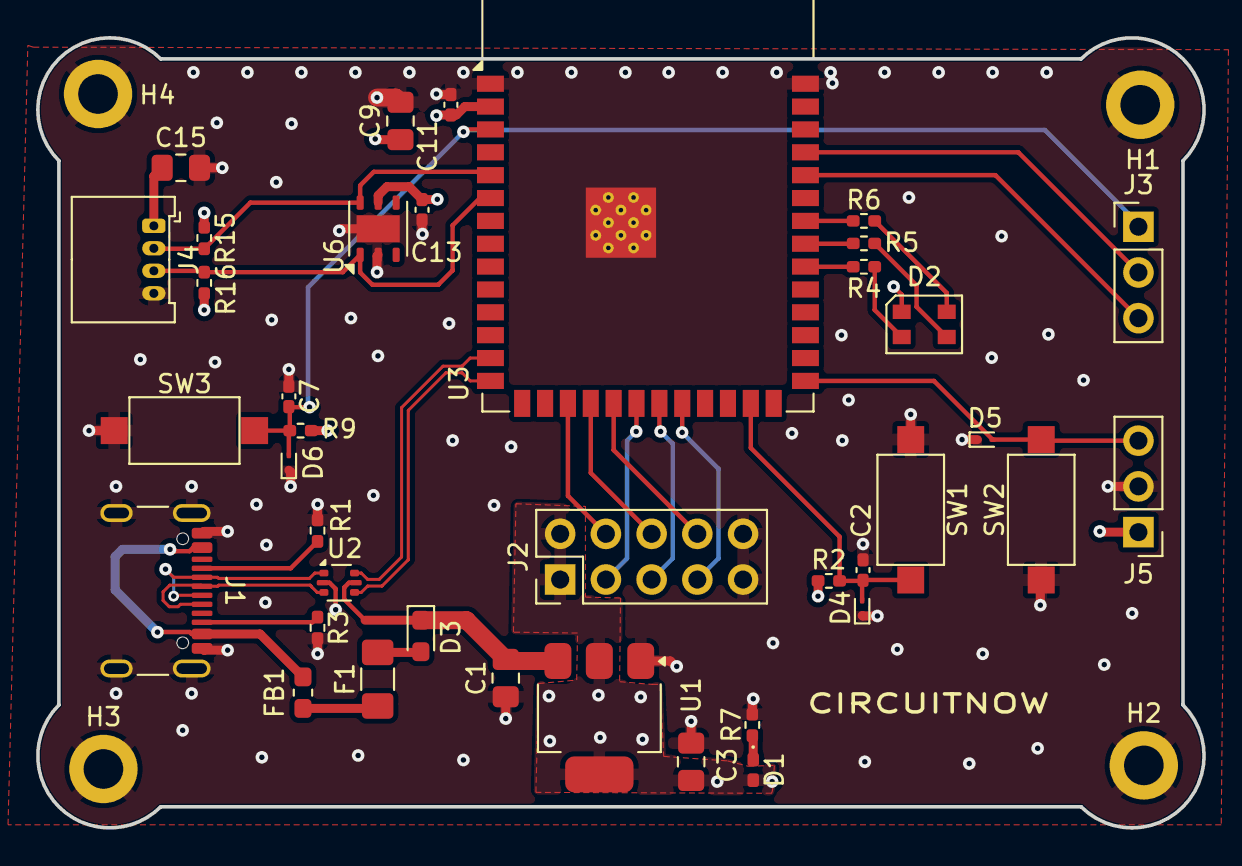
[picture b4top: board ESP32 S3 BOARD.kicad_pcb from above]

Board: 4 copper layers, 64.8 x 43.9 mm, 42 parts (0 on the bottom side), 33 nets.
